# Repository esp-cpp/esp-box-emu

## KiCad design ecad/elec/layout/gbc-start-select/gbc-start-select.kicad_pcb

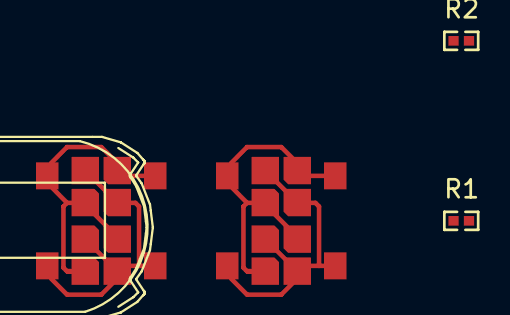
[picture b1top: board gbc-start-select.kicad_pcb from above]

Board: 2 copper layers, 5 parts (0 on the bottom side), 4 nets, no tracks yet.

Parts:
MECH1: GAMEBOY_COLOR_START_SELECT_MEMBRANE
R1, R2: 10kΩ ±5%; R0402
SW1, SW2: GBC_START_SELECT_BUTTON

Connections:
contact_in: R1.2, SW1.1, SW1.3
hv: R1.1, R2.1
lv: SW1.2, SW1.4, SW2.2, SW2.4
start_btn-out-contact_in: R2.2, SW2.1, SW2.3
